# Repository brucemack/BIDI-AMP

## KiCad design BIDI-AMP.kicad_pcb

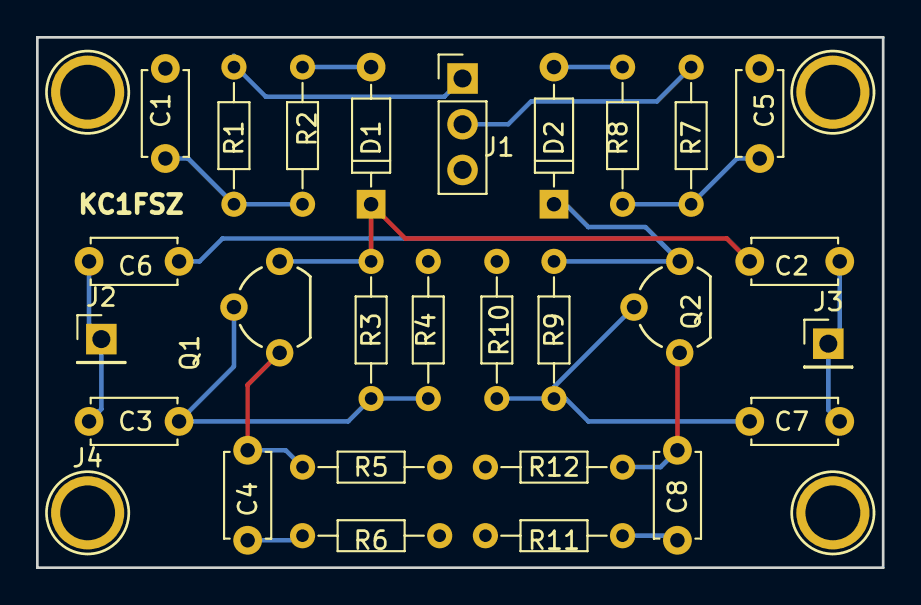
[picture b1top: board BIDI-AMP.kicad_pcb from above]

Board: 2 copper layers, 47.0 x 29.5 mm, 28 parts (0 on the bottom side), 17 nets.

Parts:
C1, C2, C3, C4, C5, C6, C7, C8: C; C_Disc_D4.7mm_W2.5mm_P5.00mm
D1, D2: D; D_DO-35_SOD27_P7.62mm_Horizontal
J1: Conn_01x03; Pin_Header_Straight_1x03_Pitch2.54mm
J2, J3: Conn_01x01; Pin_Header_Straight_1x01_Pitch2.54mm
J4: Conn_01x01; 1pin
Q1, Q2: Q_NPN_EBC; TO-92_Molded_Wide
R1, R7: 10; R_Axial_DIN0204_L3.6mm_D1.6mm_P7.62mm_Horizontal
R2, R3, R4, R5, R6, R8, R9, R10, R11, R12: R; R_Axial_DIN0204_L3.6mm_D1.6mm_P7.62mm_Horizontal

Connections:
GND: C1.2, C5.2, J1.3, J4.1, R4.2, R5.2, R6.2, R10.2, R11.2, R12.2
unnamed: C1.1, R1.1, R2.1
unnamed: C2.2, D1.1, Q1.3, R3.1
unnamed: C3.1, Q1.2, R3.2, R4.1
unnamed: C4.1, R6.1
unnamed: C4.2, Q1.1, R5.1
unnamed: C5.1, R7.1, R8.1
unnamed: C6.1, D2.1, Q2.3, R9.1
unnamed: C7.2, Q2.2, R9.2, R10.1
unnamed: C8.1, R11.1
unnamed: C8.2, Q2.1, R12.1
unnamed: D1.2, R2.2
unnamed: D2.2, R8.2
RF_LEFT: C3.2, C6.2, J2.1
RF_RIGHT: C2.1, C7.1, J3.1
RX_PWR: J1.1, R1.2
TX_PWR: J1.2, R7.2

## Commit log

2018-07-06 New layout (ground)
